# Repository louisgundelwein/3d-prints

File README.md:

# 3D prints

One folder per model, each with its own README, print files and CAD sources.

| Model | |
| --- | --- |
| [pod-v2](pod-v2/) | ESP32-C3 QR access reader prototype with a custom PCB and SolidCraft fit reference |
| [emudhra-keys](emudhra-keys/) | Wall numbers of the eight leaked eMudhra CA private keys (4 … 237), each on a hidden dovetail mount |
| [gridfinity-bolt-bins](gridfinity-bolt-bins/) | Labelled Gridfinity bins for M5/M6 screws and M3–M6 heat-set inserts |
| [meshtastic-node](meshtastic-node/) | TPU case for a USB-C Meshtastic node (ESP32 + SX1262), with wired board models |
| [mac-mini-rack-v2](mac-mini-rack-v2/) | 3U rack for four Mac mini (M4), two stacks of two |
| [mac-mini-rack-v1](mac-mini-rack-v1/) | 3U rack for four Mac mini (M4) on their sides, with TPU strips (superseded by v2) |

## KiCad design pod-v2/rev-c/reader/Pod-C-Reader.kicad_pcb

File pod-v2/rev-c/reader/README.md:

# Rev C outdoor reader

The 72 × 100 mm reader retains the Rev B scanner opening, mounting holes, front LED ring and NFC antenna clearance. Open [Pod-C-Reader.kicad_pro](Pod-C-Reader.kicad_pro) in KiCad 9. See [Rev B scanner and NFC assembly](../../rev-b/pcb/README.md#assembly-and-cables) for the optical engine, flex and keyed module harness.

| Connector | Contacts |
| --- | --- |
| J1 bench power | 1 regulated 5 V, 2 GND |
| J2 scanner flex | 2 3.3 V, 3 GND, 4 host TX, 5 engine TX, 12 active-low trigger. Other contacts open. |
| J3 RS-485 | 1 A (noninverting), 2 B (inverting), 3 signal GND. 120 Ω across A/B on the board. |
| J4 programming UART | 1 GND, 2 host TX, 3 host RX. Use 3.3 V serial levels. |
| J5 NFC | 1 open, 2 SDA, 3 SCL, 4 IRQ, 5 VEN, 6 3.3 V, 7 GND, 8 5 V |

| Function | ESP32-C3 GPIO |
| --- | --- |
| Bus UART0 TX / RX / direction | 18 / 19 / 3 |
| UART0 ROM programming TX / RX | 21 / 20 |
| Scanner UART1 TX / RX | 4 / 5 |
| NFC SDA / SCL / IRQ / VEN | 0 / 1 / 6 / 7 |
| RGB pixel data | 10 |

Remap UART0 to GPIO18/19 in application firmware and disable the UART0 application console so log bytes stay off the bus. GPIO18/19 are the native USB pins. Use J4 for ROM download. GPIO3 is pulled low at reset, enabling receiver mode with the transmitter disabled. [ESP32-C3 module](https://documentation.espressif.com/esp32-c3-mini-1_datasheet_en.html) · [THVD1410](https://www.ti.com/product/THVD1410)

Start at 5.0 V measured at J1 with a regulated current-limited bench supply. Check that the TRACO input and NFC VANT remain at least 4.75 V at full combined load and measure scanner supply ripple (50 mV peak-to-peak maximum). This board is for a controlled, short, common-ground bus. The actual run needs cable, grounding and surge validation. [TRACO TSR 1](https://www.tracopower.com/products/tsr1.pdf) · [ELECHOUSE](https://www.elechouse.com/docs/pn7160/) · [Newland integration guide](https://newlandemea.katanapim.com/AttachmentDownload/Download/688?name=EM3080-W+V2_Integration+Guide_V1+2026.pdf)

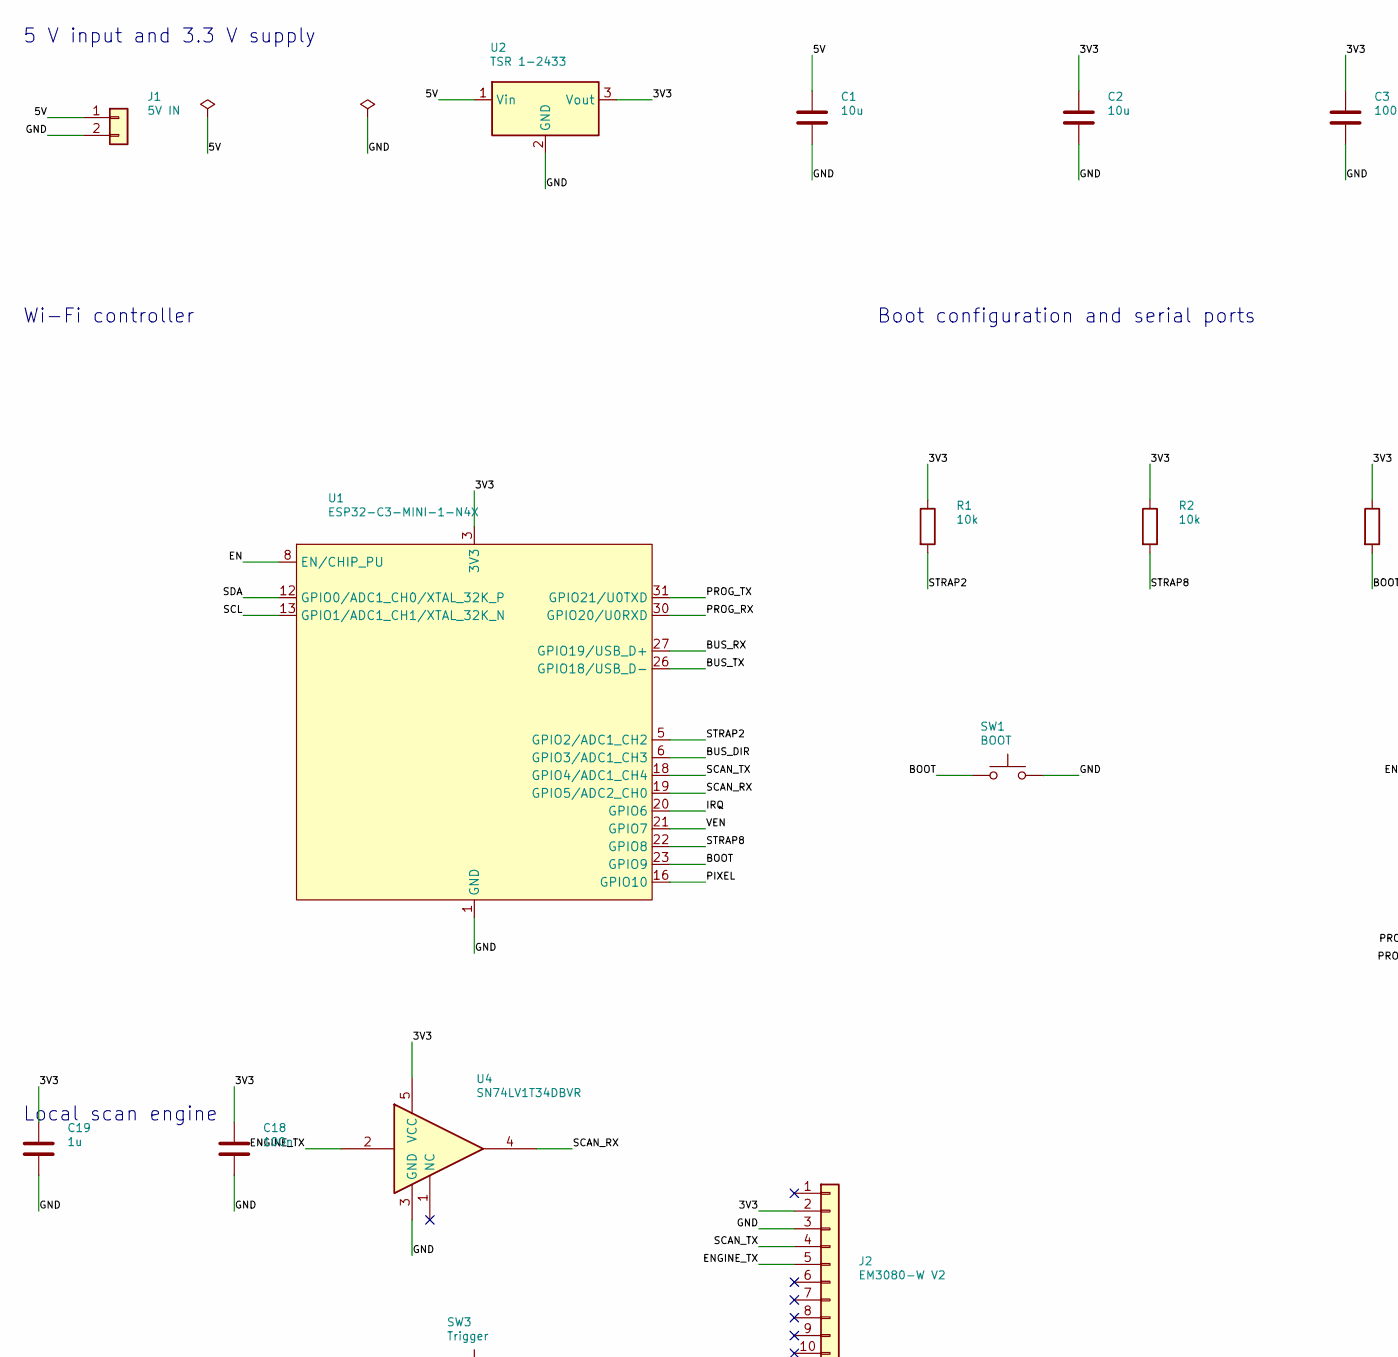
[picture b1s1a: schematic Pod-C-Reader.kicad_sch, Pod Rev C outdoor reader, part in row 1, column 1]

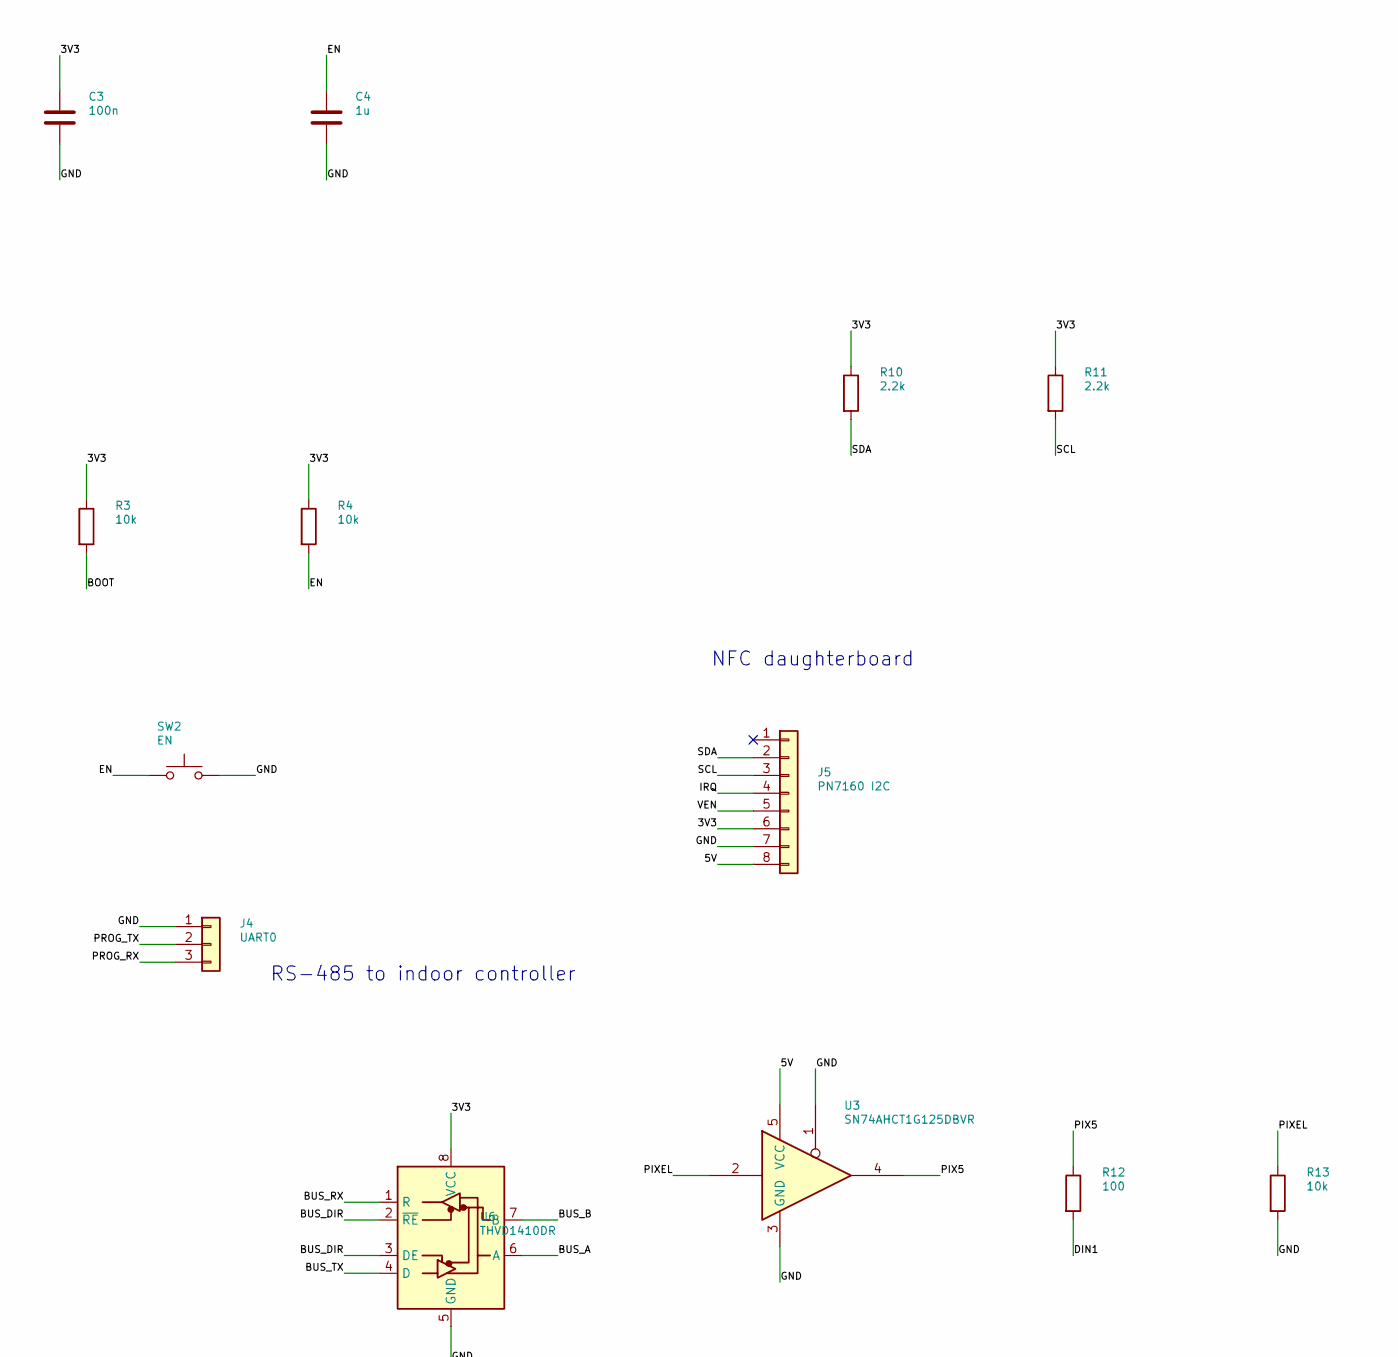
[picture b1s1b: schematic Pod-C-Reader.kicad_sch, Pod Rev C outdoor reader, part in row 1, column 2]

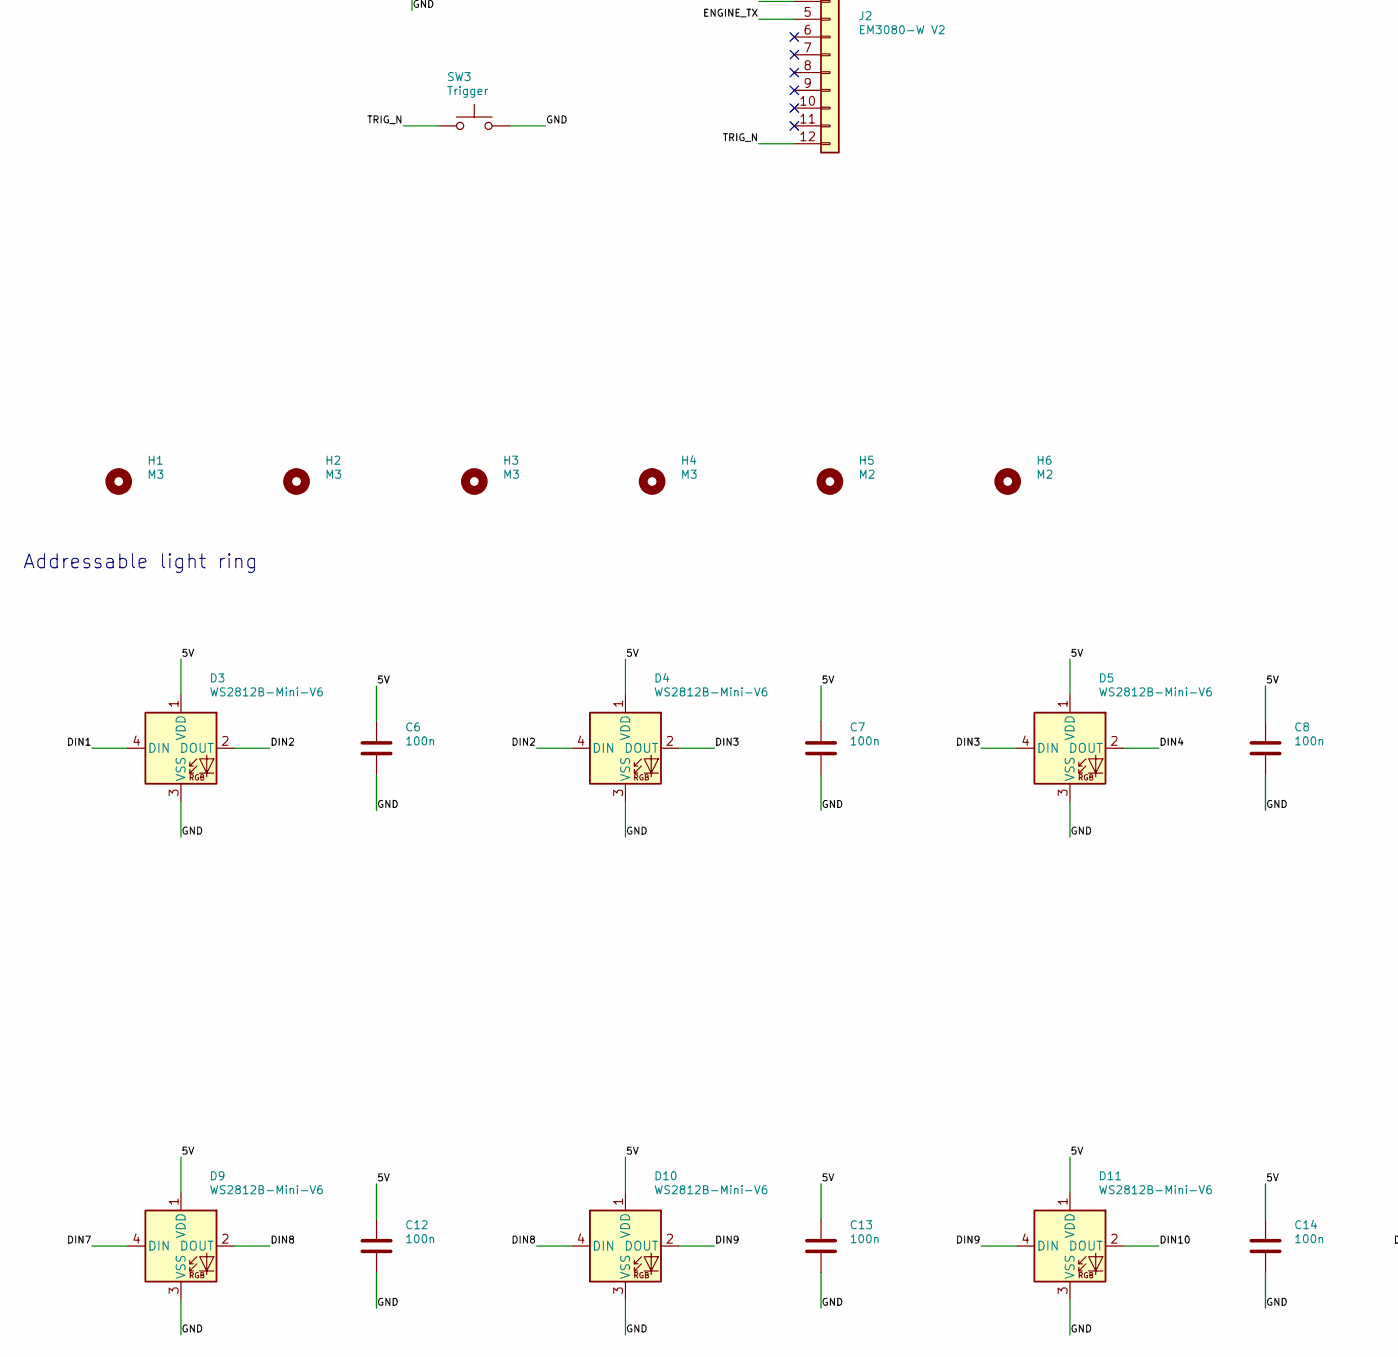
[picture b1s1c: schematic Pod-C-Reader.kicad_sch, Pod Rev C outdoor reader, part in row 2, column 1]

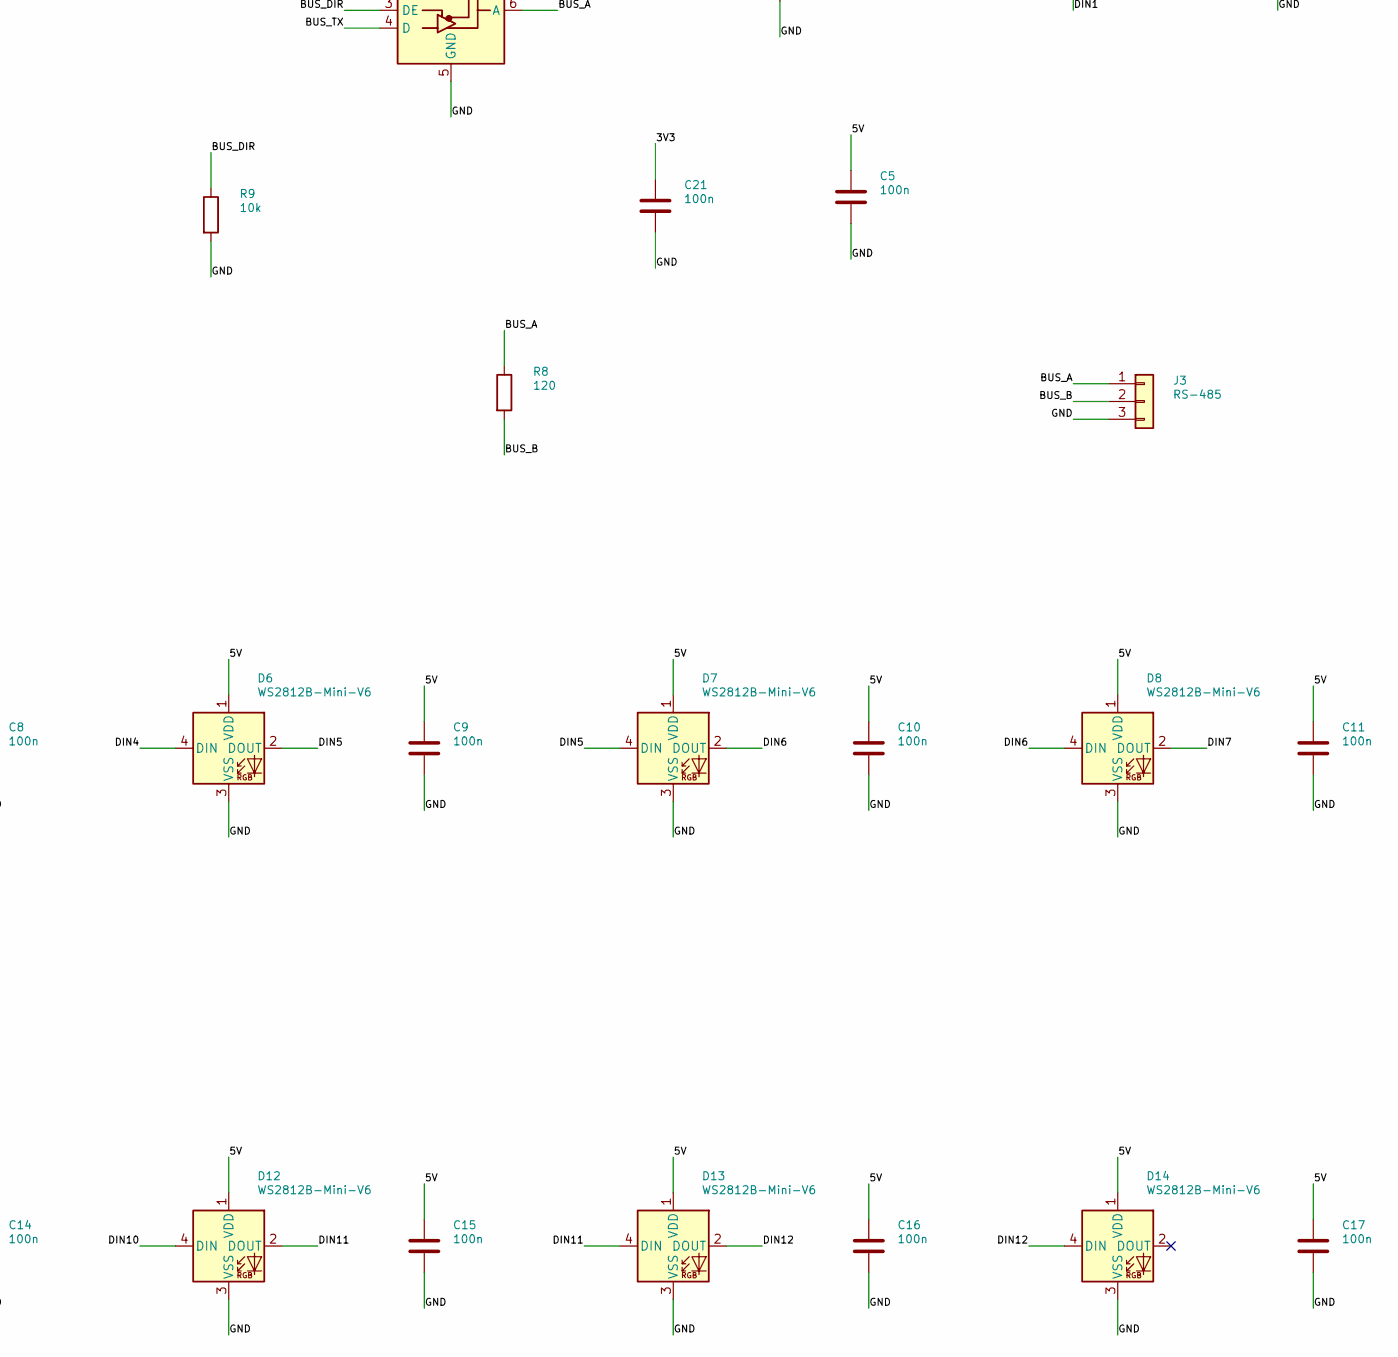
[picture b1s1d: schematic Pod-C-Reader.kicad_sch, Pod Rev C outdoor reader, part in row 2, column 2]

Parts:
C1, C2: 10u; C_1206_3216Metric
C3, C5, C6, C7, C8, C9, C10, C11, C12, C13, C14, C15, C16, C17, C18, C21: 100n; C_0805_2012Metric
C4, C19: 1u; C_0805_2012Metric
D3, D4, D5, D6, D7, D8, D9, D10, D11, D12, D13, D14: WS2812B-Mini-V6; LED_WS2812B-Mini_PLCC4_3.5x3.5mm
H1, H2, H3, H4: M3; MountingHole_3.2mm_M3
H5, H6: M2; MountingHole_2.2mm_M2
J1: 5V IN; PinHeader_1x02_P2.54mm_Vertical
J2: EM3080-W V2; Hirose_FH12-12S-0.5SH_1x12-1MP_P0.50mm_Horizontal
J3: RS-485; TerminalBlock_Phoenix_MKDS-1,5-3-5.08_1x03_P5.08mm_Horizont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
J4: UART0; PinHeader_1x03_P2.54mm_Vertical
J5: PN7160 I2C; JST_GH_SM08B-GHS-TB_1x08-1MP_P1.25mm_Horizontal
R1, R2, R3, R4, R9, R13: 10k; R_0805_2012Metric
R8: 120; R_0805_2012Metric
R10, R11: 2.2k; R_0805_2012Metric
R12: 100; R_0805_2012Metric
SW1: BOOT; SW_Push_1P1T_NO_CK_KMR2
SW2: EN; SW_Push_1P1T_NO_CK_KMR2
SW3: Trigger; SW_Push_1P1T_NO_CK_KMR2
U1: ESP32-C3-MINI-1-N4X; ESP32-C3-MINI-1
U2: TSR 1-2433; Converter_DCDC_TRACO_TSR-1_THT
U3: SN74AHCT1G125DBVR; SOT-23-5
U4: SN74LV1T34DBVR; SOT-23-5
U6: THVD1410DR; SOIC-8_3.9x4.9mm_P1.27mm

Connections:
/3V3: C2.1, C3.1, C18.1, C19.1, C21.1, J2.2, J5.6, R1.1, R2.1, R3.1, R4.1, R10.1, R11.1, U1.3 (3V3), U2.3 (Vout), U4.5 (VCC), U6.8 (VCC)
/5V: C1.1, C5.1, C6.1, C7.1, C8.1, C9.1, C10.1, C11.1, C12.1, C13.1, C14.1, C15.1, C16.1, C17.1, D3.1 (VDD), D4.1 (VDD), D5.1 (VDD), D6.1 (VDD), D7.1 (VDD), D8.1 (VDD), D9.1 (VDD), D10.1 (VDD), D11.1 (VDD), D12.1 (VDD), D13.1 (VDD), D14.1 (VDD), J1.1, J5.8, U2.1 (Vin), U3.5 (VCC)
/BOOT: R3.2, SW1.1, U1.23 (GPIO9)
/BUS_A: J3.1, R8.1, U6.6 (A)
/BUS_B: J3.2, R8.2, U6.7 (B)
/BUS_DIR: R9.1, U1.6 (GPIO3/ADC1_CH3), U6.2 (~RE), U6.3 (DE)
/BUS_RX: U1.27 (GPIO19/USB_D+), U6.1 (R)
/BUS_TX: U1.26 (GPIO18/USB_D-), U6.4 (D)
/DIN1: D3.4 (DIN), R12.2
/DIN2: D3.2 (DOUT), D4.4 (DIN)
/DIN3: D4.2 (DOUT), D5.4 (DIN)
/DIN4: D5.2 (DOUT), D6.4 (DIN)
/DIN5: D6.2 (DOUT), D7.4 (DIN)
/DIN6: D7.2 (DOUT), D8.4 (DIN)
/DIN7: D8.2 (DOUT), D9.4 (DIN)
/DIN8: D9.2 (DOUT), D10.4 (DIN)
/DIN9: D10.2 (DOUT), D11.4 (DIN)
/DIN10: D11.2 (DOUT), D12.4 (DIN)
/DIN11: D12.2 (DOUT), D13.4 (DIN)
/DIN12: D13.2 (DOUT), D14.4 (DIN)
/EN: C4.1, R4.2, SW2.1, U1.8 (EN/CHIP_PU)
/ENGINE_TX: J2.5, U4.2
/IRQ: J5.4, U1.20 (GPIO6)
/PIX5: R12.1, U3.4
/PIXEL: R13.1, U1.16 (GPIO10), U3.2
/PROG_RX: J4.3, U1.30 (GPIO20/U0RXD)
/PROG_TX: J4.2, U1.31 (GPIO21/U0TXD)
/SCAN_RX: U1.19 (GPIO5/ADC2_CH0), U4.4
/SCAN_TX: J2.4, U1.18 (GPIO4/ADC1_CH4)
/SCL: J5.3, R11.2, U1.13 (GPIO1/ADC1_CH1/XTAL_32K_N)
/SDA: J5.2, R10.2, U1.12 (GPIO0/ADC1_CH0/XTAL_32K_P)
/STRAP2: R1.2, U1.5 (GPIO2/ADC1_CH2)
/STRAP8: R2.2, U1.22 (GPIO8)
/TRIG_N: J2.12, SW3.1
/VEN: J5.5, U1.21 (GPIO7)
GND: C1.2, C2.2, C3.2, C4.2, C5.2, C6.2, C7.2, C8.2, C9.2, C10.2, C11.2, C12.2, C13.2, C14.2, C15.2, C16.2, C17.2, C18.2, C19.2, C21.2, D3.3 (VSS), D4.3 (VSS), D5.3 (VSS), D6.3 (VSS), D7.3 (VSS), D8.3 (VSS), D9.3 (VSS), D10.3 (VSS), D11.3 (VSS), D12.3 (VSS), D13.3 (VSS), D14.3 (VSS), J1.2, J2.3, J3.3, J4.1, J5.7, R9.2, R13.2, SW1.2, SW2.2, SW3.2, U1.1 (GND), U1.2 (GND), U1.11 (GND), U1.14 (GND), U1.36 (GND), U1.37 (GND), U1.38 (GND), U1.39 (GND), U1.40 (GND), U1.41 (GND), U1.42 (GND), U1.43 (GND), U1.44 (GND), U1.45 (GND), U1.46 (GND), U1.47 (GND), U1.48 (GND), U1.49 (GND), U1.50 (GND), U1.51 (GND), U1.52 (GND), U1.53 (GND), U2.2 (GND), U3.1, U3.3 (GND), U4.3 (GND), U6.5 (GND)

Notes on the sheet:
5 V input and 3.3 V supply
Wi-Fi controller
Boot configuration and serial ports
Local scan engine
Addressable light ring
NFC daughterboard
RS-485 to indoor controller

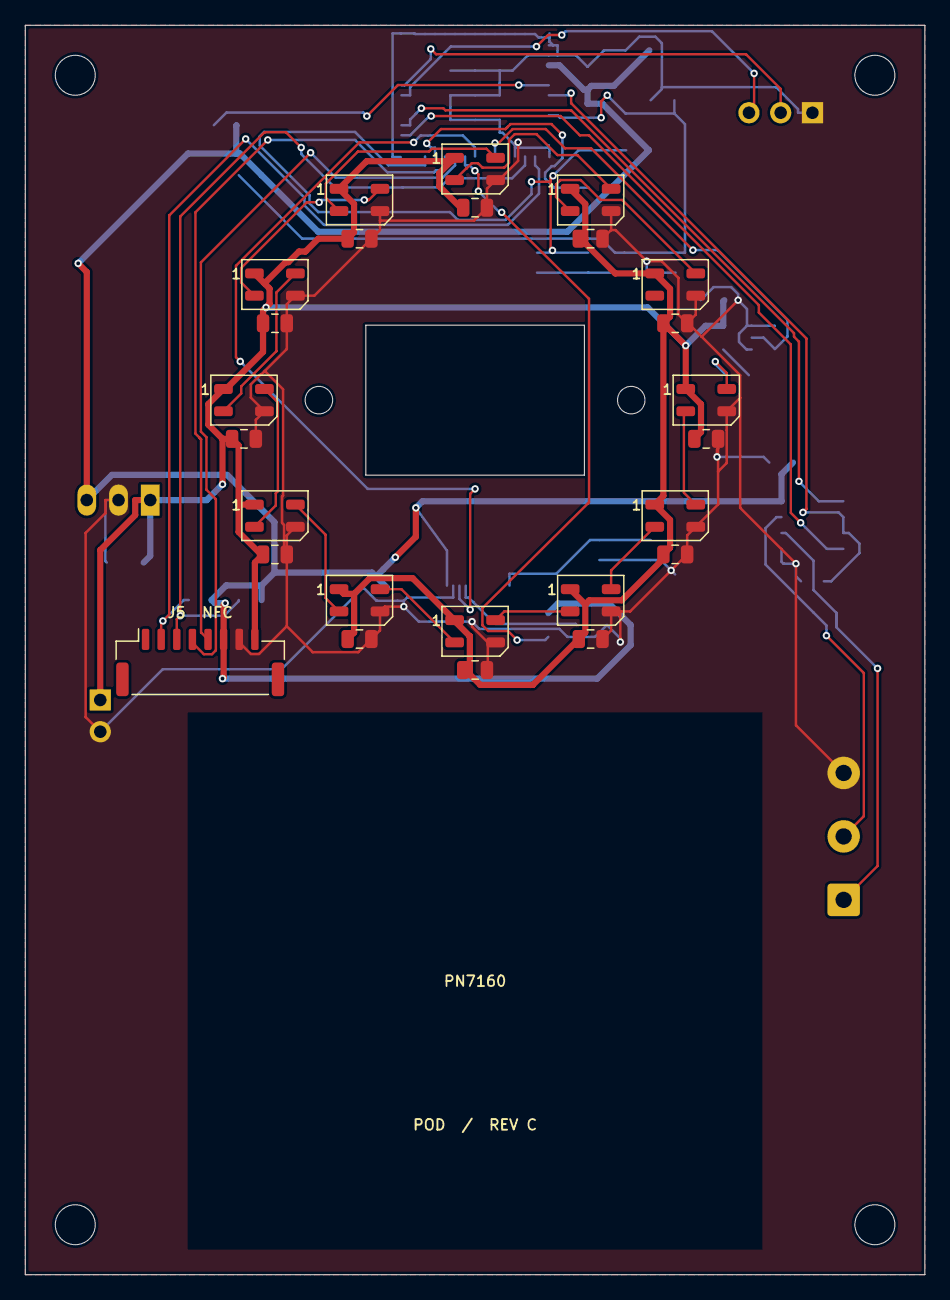
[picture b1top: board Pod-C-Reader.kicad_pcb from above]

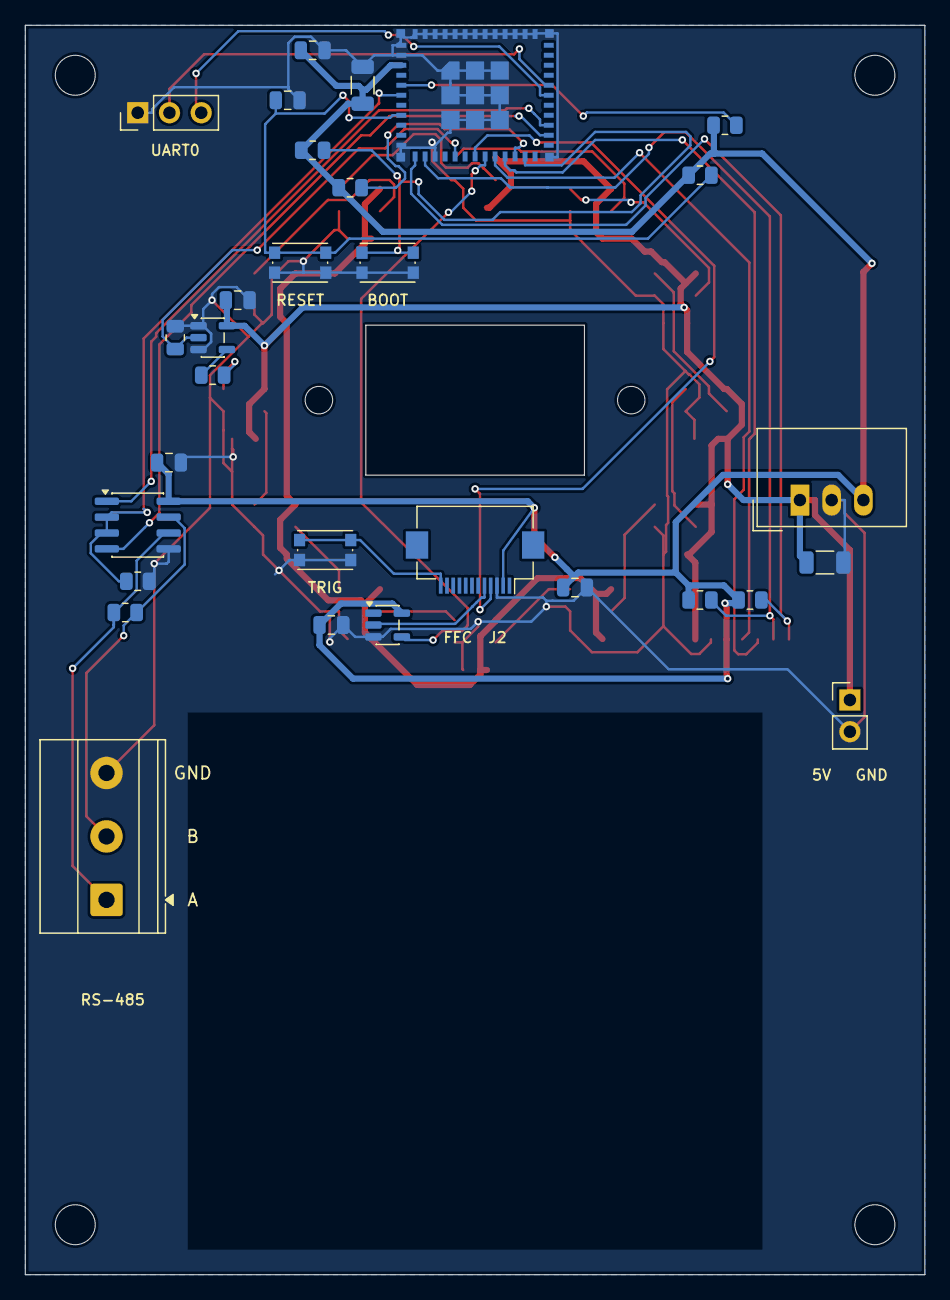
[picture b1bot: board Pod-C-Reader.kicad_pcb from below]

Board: 2 copper layers, 72.0 x 100.0 mm, 61 parts (30 on the bottom side), 36 nets.

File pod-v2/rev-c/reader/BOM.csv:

References,Quantity,Part or specification,Footprint
J1,1,"1x02 pin header, 2.54 mm",Connector_PinHeader_2.54mm:PinHeader_1x02_P2.54mm_Vertical
U2,1,TSR 1-2433,Converter_DCDC:Converter_DCDC_TRACO_TSR-1_THT
C1 C2,2,10uF X7R 16V,Capacitor_SMD:C_1206_3216Metric
C3 C5 C18 C6 C7 C8 C9 C10 C11 C12 C13 C14 C15 C16 C17 C21,16,100nF X7R 16V,Capacitor_SMD:C_0805_2012Metric
C4 C19,2,1uF X7R 16V,Capacitor_SMD:C_0805_2012Metric
U1,1,ESP32-C3-MINI-1-N4X,Pod:ESP32-C3-MINI-1
R1 R2 R3 R4 R9 R13,6,10k ohm 1%,Resistor_SMD:R_0805_2012Metric
SW1 SW2 SW3,3,C&K KMR221G LFS,Button_Switch_SMD:SW_Push_1P1T_NO_CK_KMR2
J2,1,Hirose FH12-12S-0.5SH(55),Connector_FFC-FPC:Hirose_FH12-12S-0.5SH_1x12-1MP_P0.50mm_Horizontal
J5,1,JST SM08B-GHS-TB(LF)(SN),Connector_JST:JST_GH_SM08B-GHS-TB_1x08-1MP_P1.25mm_Horizontal
R10 R11,2,2.2k ohm 1%,Resistor_SMD:R_0805_2012Metric
U3,1,SN74AHCT1G125DBVR,Package_TO_SOT_SMD:SOT-23-5
U4,1,SN74LV1T34DBVR,Package_TO_SOT_SMD:SOT-23-5
D3 D4 D5 D6 D7 D8 D9 D10 D11 D12 D13 D14,12,WS2812B-Mini-V6,LED_SMD:LED_WS2812B-Mini_PLCC4_3.5x3.5mm
J4,1,"1x03 pin header, 2.54 mm",Connector_PinHeader_2.54mm:PinHeader_1x03_P2.54mm_Vertical
J3,1,"Phoenix Contact 1715734 (MKDS 1,5/3-5,08)","TerminalBlock_Phoenix:TerminalBlock_Phoenix_MKDS-1,5-3-5.08_1x03_P5.08mm_Horizontal"
U6,1,THVD1410DR,Package_SO:SOIC-8_3.9x4.9mm_P1.27mm
R8,1,120 ohm 1%,Resistor_SMD:R_0805_2012Metric
R12,1,100 ohm 1%,Resistor_SMD:R_0805_2012Metric
Assembly,1,Newland NLS-EM3080-W V2,Scanner cradle
Assembly,1,"12-way 0.5 mm FFC, reinforced ends",J2 to scanner; verify exposure and length
Assembly,1,ELECHOUSE PN7160 I2C module,Front antenna cradle
Assembly,1,JST GHR-08V-S to supplied ELECHOUSE 8-way harness,J5 to module

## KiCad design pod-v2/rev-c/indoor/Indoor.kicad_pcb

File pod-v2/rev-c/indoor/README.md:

# Rev C indoor laboratory node

52 × 74 mm, two copper layers. Protected indoor bench prototype. The antenna overhangs the upper board edge by 5.4 mm; keep the antenna free of metal, enclosure hardware and wiring. Housing and RF performance require physical validation.

**Lab dummy load only until authorization is implemented and validated. Never connect live entry/access systems. Firmware, authorization, production installation and live entry testing are outside this design.**

## Wiring

| Connector | Pin | Connection |
|---|---|---|
| J1 | 1 / 2 | Regulated bench +5 V / GND |
| J2 Phoenix MKDS 5.08 mm | 1 | RS485 A, noninverting |
| J2 | 2 | RS485 B, inverting |
| J2 | 3 | GND reference, never supply power |
| J3 Phoenix MKDS 5.08 mm | 1 / 2 | Dry-contact COM / normally open NO |
| J4 UART0 | 1 / 2 / 3 | GND / GPIO21 TX / GPIO20 RX |
| J5 JST PH keyed | 1 / 2 | CR2032 primary battery positive / GND |

J1 uses a 2.54 mm pin header. Connect a separate regulated 5 V bench supply; do not backfeed through UART or RS485. UART logic is 3.3 V; cross TX/RX to the adapter. J3 carries low-voltage dummy loads only; no mains and no door strike. The relay coil has a flyback diode; external inductive loads require their own suppression.

The RS485 end has fixed 120 Ω termination across A/B. Use only as a physical bus endpoint. GND is the common reference; there is no galvanic isolation, external surge protection or outdoor cable rating. THVD1410DR runs from 3.3 V. GPIO4 TX and GPIO5 RX map to UART1 in future firmware; GPIO10 drives tied DE and /RE, with a 10 kΩ pulldown. Idle defaults to receive.

GPIO3 drives the AO3400A relay transistor through 100 Ω. Both the GPIO and gate have external 10 kΩ pulldowns. G5V-1 DC5 COM uses pins 5 and 6, NO uses pin 10, unused NC is disconnected. Power, boot/reset and relay topology follow Rev B.

The sole RTC is DS3231MZ+, indoors. SDA GPIO0, SCL GPIO1; both have 2.2 kΩ pullups to the switched 3.3 V rail. CR2032 connects directly to VBAT through the keyed cable connector. Assumption: an insulated cabled CR2032 holder is fitted inside the enclosure. No charging circuit is fitted. Use a primary CR2032, not a rechargeable cell. Pins 1, 3 and 4 of the RTC are intentionally disconnected.

## Checks and limits

KiCad 9 schematic and routed PCB are provided with project-local ESP32 footprint and symbols. BOM.csv lists each fitted part and footprint. ERC and DRC reports in checks/ include schematic parity. These checks do not replace independent electrical review, assembly inspection, antenna testing, thermal/current validation or hardware bring-up. No board was fabricated or powered.

THVD1410 pin assignment checked against https://www.ti.com/lit/ds/symlink/thvd1410.pdf .

Final KiCad 9 checks: ERC 0 errors/0 warnings; DRC 0 violations, 0 unconnected pads, 0 schematic parity issues. No exclusions were introduced. Final layout is stable for independent review.

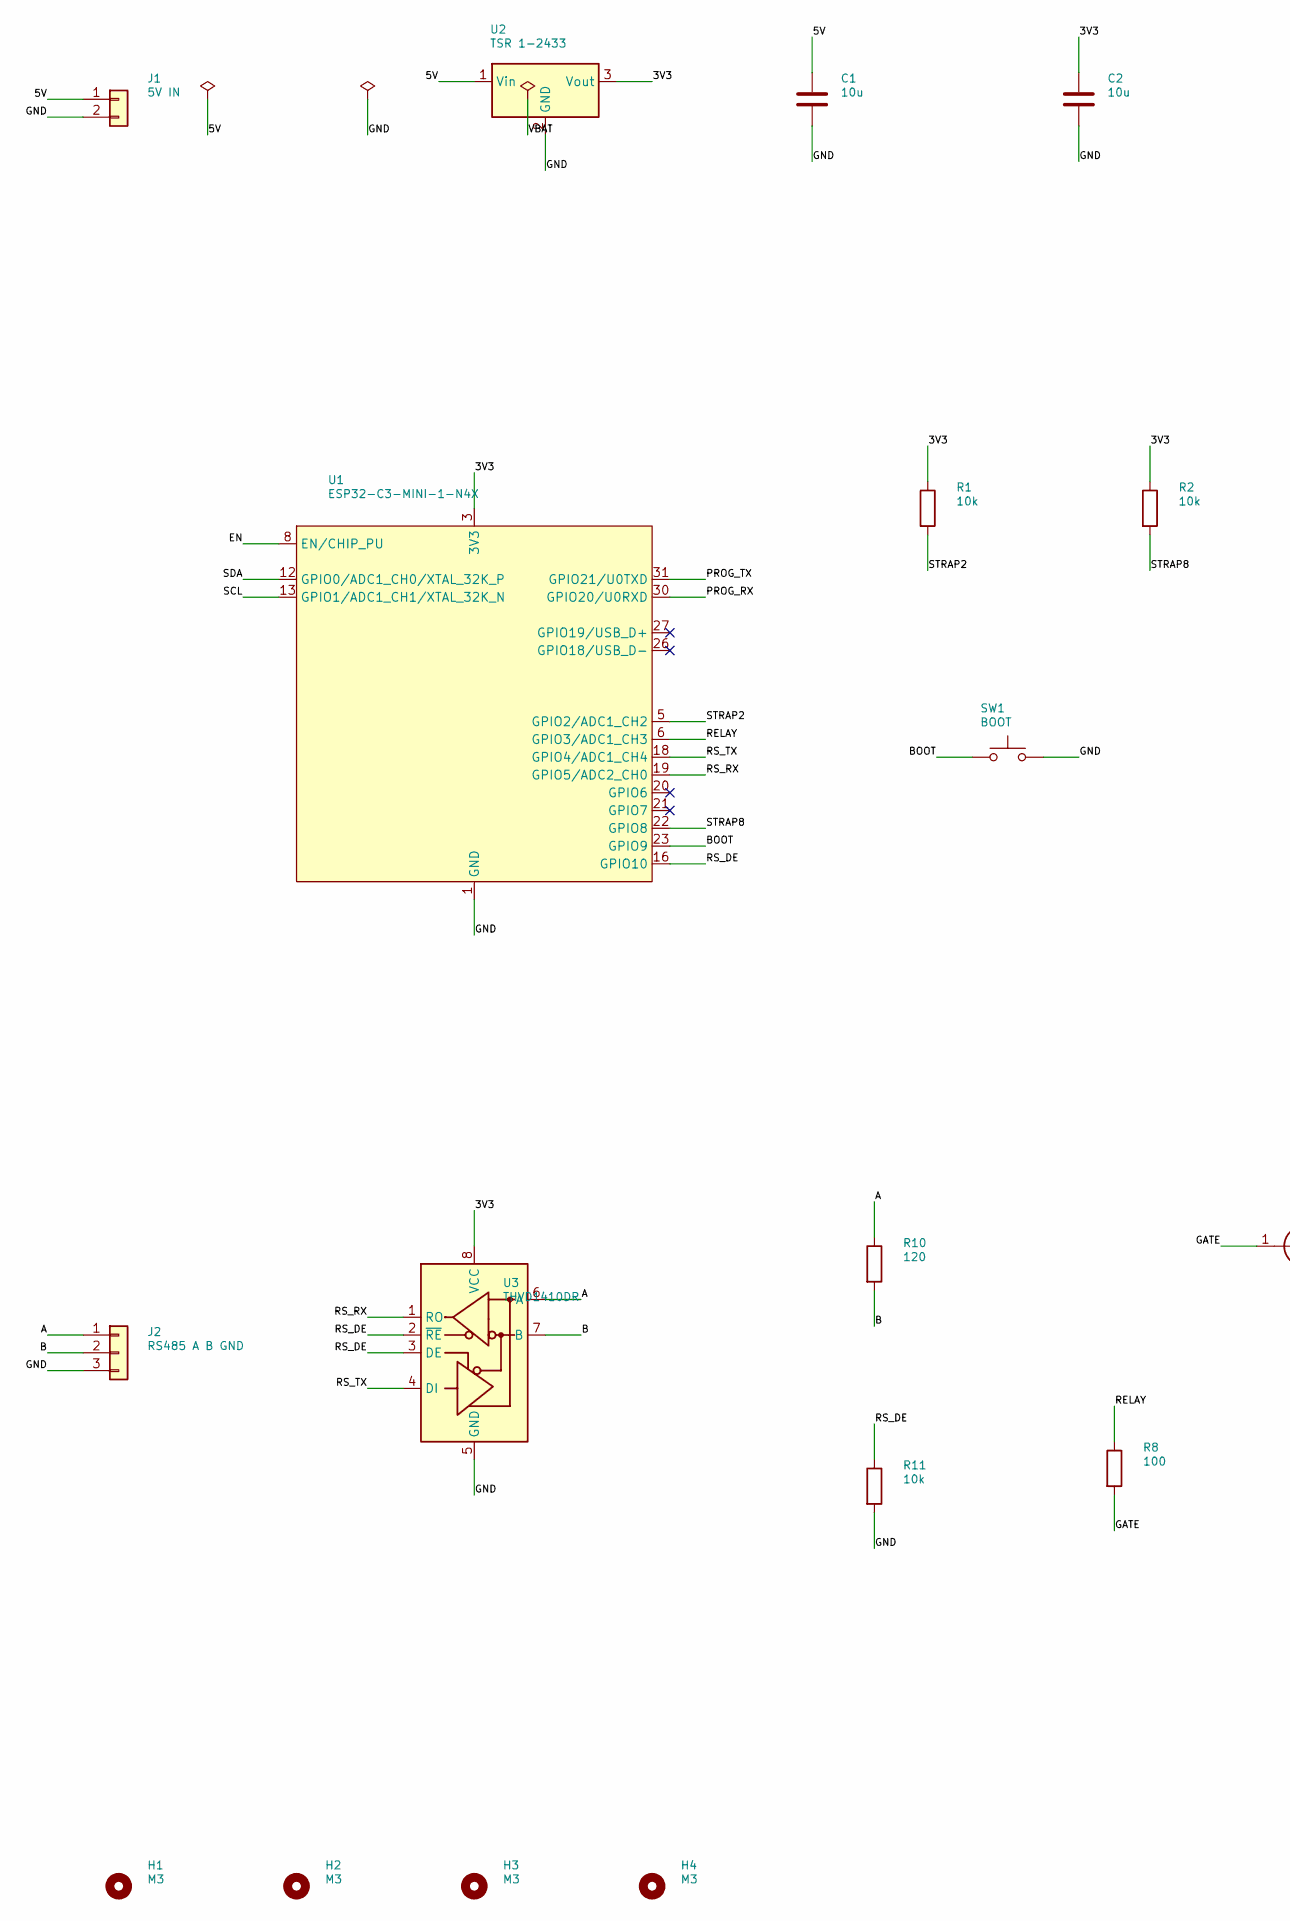
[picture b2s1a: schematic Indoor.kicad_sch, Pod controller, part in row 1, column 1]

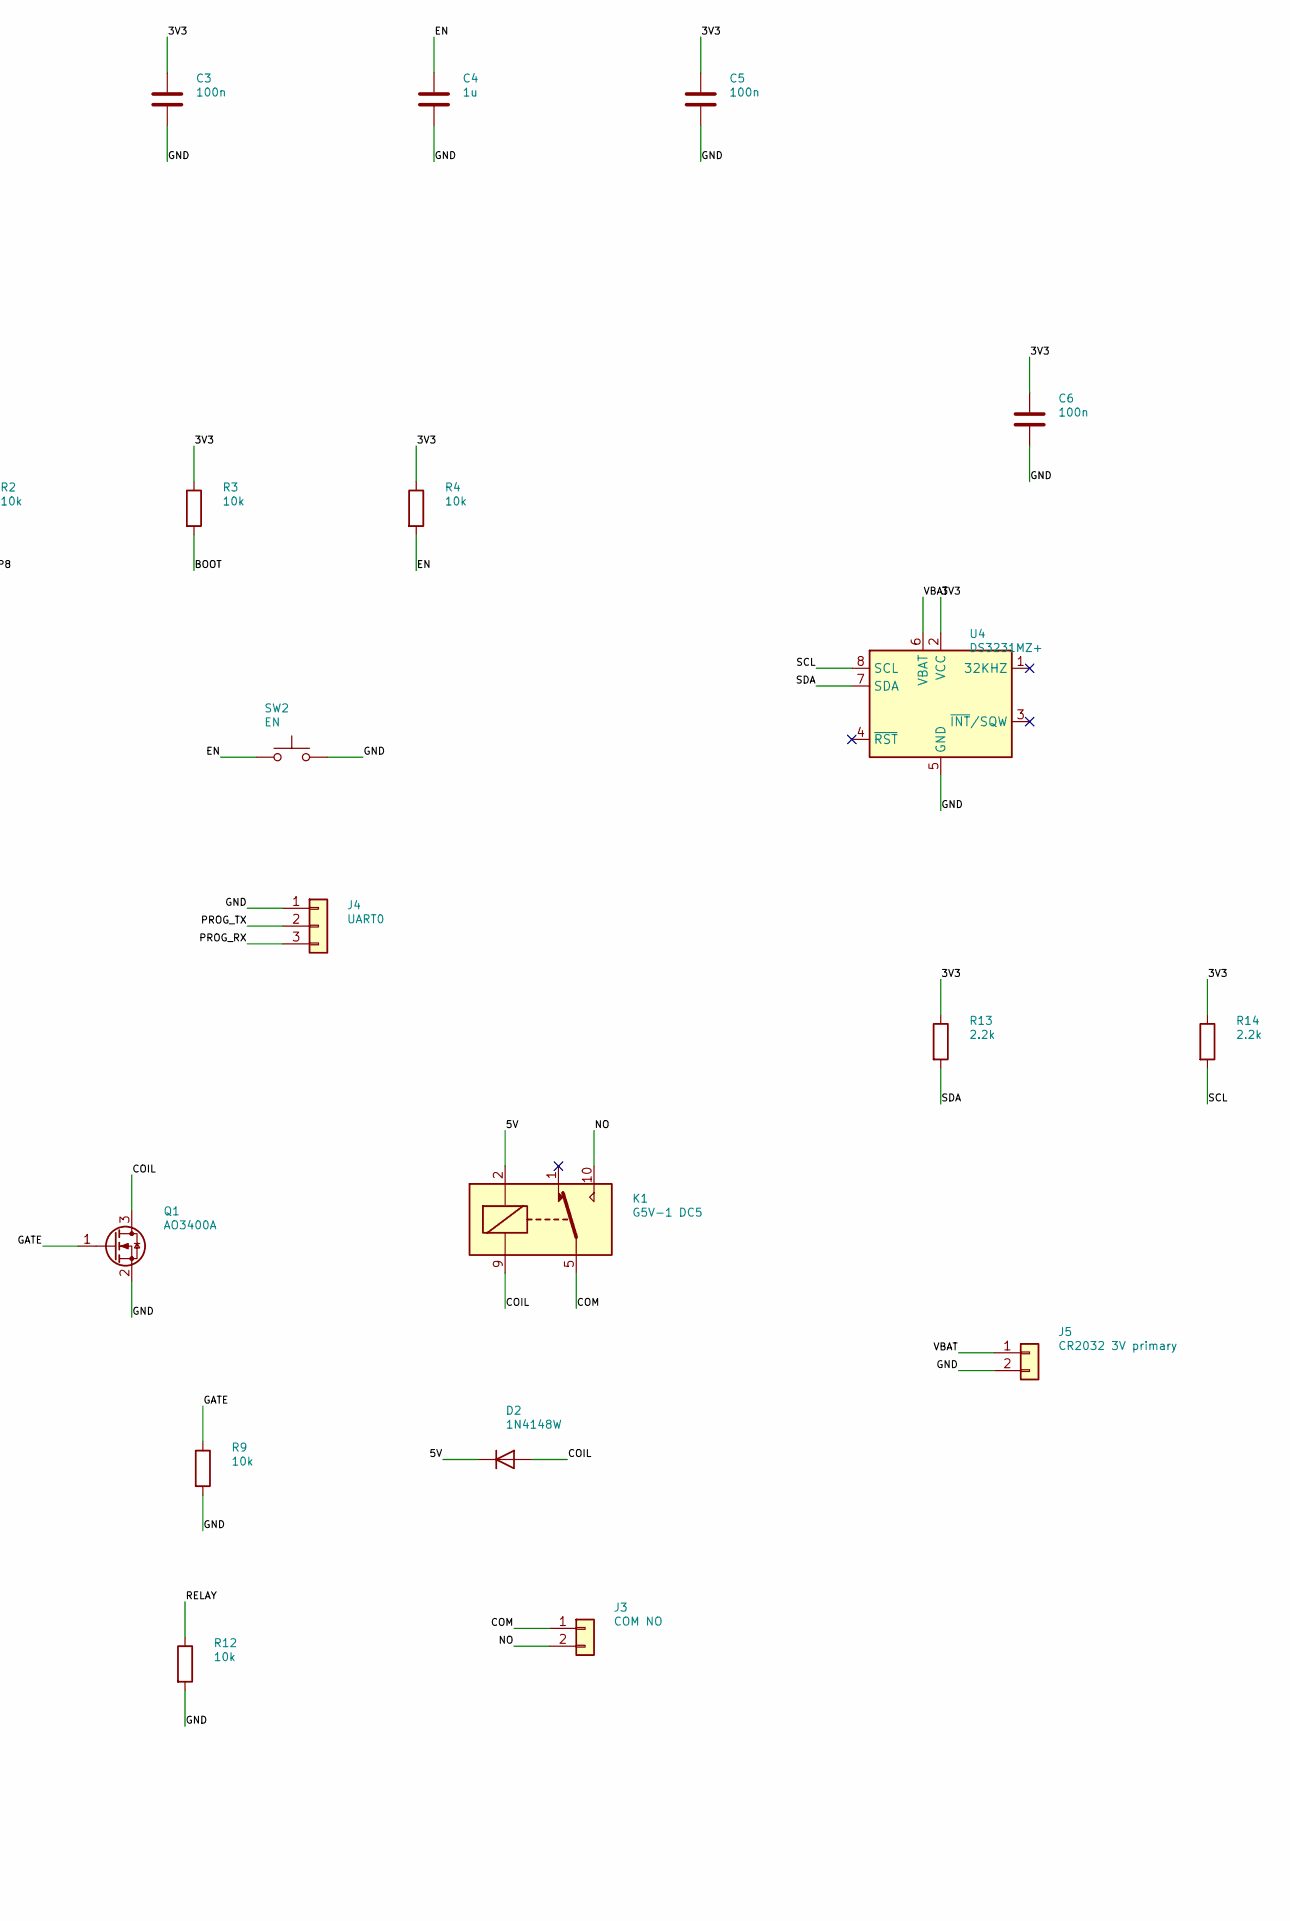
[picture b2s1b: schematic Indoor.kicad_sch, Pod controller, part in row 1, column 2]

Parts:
C1, C2: 10u; C_1206_3216Metric
C3, C5, C6: 100n; C_0805_2012Metric
C4: 1u; C_0805_2012Metric
D2: 1N4148W; D_SOD-123
H1, H2, H3, H4: M3; MountingHole_3.2mm_M3
J1: 5V IN; PinHeader_1x02_P2.54mm_Vertical
J2: RS485 A B GND; TerminalBlock_Phoenix_MKDS-1,5-3-5.08_1x03_P5.08mm_Horizont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
J3: COM NO; TerminalBlock_Phoenix_MKDS-1,5-2-5.08_1x02_P5.08mm_Horizont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
J4: UART0; PinHeader_1x03_P2.54mm_Vertical
J5: CR2032 3V primary; JST_PH_B2B-PH-K_1x02_P2.00mm_Vertical
K1: G5V-1 DC5; Relay_SPDT_Omron_G5V-1
Q1: AO3400A; SOT-23
R1, R2, R3, R4, R9, R11, R12: 10k; R_0805_2012Metric
R8: 100; R_0805_2012Metric
R10: 120; R_0805_2012Metric
R13, R14: 2.2k; R_0805_2012Metric
SW1: BOOT; SW_Push_1P1T_NO_CK_KMR2
SW2: EN; SW_Push_1P1T_NO_CK_KMR2
U1: ESP32-C3-MINI-1-N4X; ESP32-C3-MINI-1
U2: TSR 1-2433; Converter_DCDC_TRACO_TSR-1_THT
U3: THVD1410DR; SOIC-8_3.9x4.9mm_P1.27mm
U4: DS3231MZ+; SOIC-8_3.9x4.9mm_P1.27mm

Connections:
/3V3: C2.1, C3.1, C5.1, C6.1, R1.1, R2.1, R3.1, R4.1, R13.1, R14.1, U1.3 (3V3), U2.3 (Vout), U3.8 (VCC), U4.2 (VCC)
/5V: C1.1, D2.1 (K), J1.1, K1.2, U2.1 (Vin)
/A: J2.1, R10.1, U3.6 (A)
/B: J2.2, R10.2, U3.7 (B)
/BOOT: R3.2, SW1.1, U1.23 (GPIO9)
/COIL: D2.2 (A), K1.9, Q1.3 (D)
/COM: J3.1, K1.5, K1.6
/EN: C4.1, R4.2, SW2.1, U1.8 (EN/CHIP_PU)
/GATE: Q1.1 (G), R8.2, R9.1
/NO: J3.2, K1.10
/PROG_RX: J4.3, U1.30 (GPIO20/U0RXD)
/PROG_TX: J4.2, U1.31 (GPIO21/U0TXD)
/RELAY: R8.1, R12.1, U1.6 (GPIO3/ADC1_CH3)
/RS_DE: R11.1, U1.16 (GPIO10), U3.2 (~RE), U3.3 (DE)
/RS_RX: U1.19 (GPIO5/ADC2_CH0), U3.1 (RO)
/RS_TX: U1.18 (GPIO4/ADC1_CH4), U3.4 (DI)
/SCL: R14.2, U1.13 (GPIO1/ADC1_CH1/XTAL_32K_N), U4.8 (SCL)
/SDA: R13.2, U1.12 (GPIO0/ADC1_CH0/XTAL_32K_P), U4.7 (SDA)
/STRAP2: R1.2, U1.5 (GPIO2/ADC1_CH2)
/STRAP8: R2.2, U1.22 (GPIO8)
/VBAT: J5.1, U4.6 (VBAT)
GND: C1.2, C2.2, C3.2, C4.2, C5.2, C6.2, J1.2, J2.3, J4.1, J5.2, Q1.2 (S), R9.2, R11.2, R12.2, SW1.2, SW2.2, U1.1 (GND), U1.2 (GND), U1.11 (GND), U1.14 (GND), U1.36 (GND), U1.37 (GND), U1.38 (GND), U1.39 (GND), U1.40 (GND), U1.41 (GND), U1.42 (GND), U1.43 (GND), U1.44 (GND), U1.45 (GND), U1.46 (GND), U1.47 (GND), U1.48 (GND), U1.49 (GND), U1.50 (GND), U1.51 (GND), U1.52 (GND), U1.53 (GND), U2.2 (GND), U3.5 (GND), U4.5 (GND)
